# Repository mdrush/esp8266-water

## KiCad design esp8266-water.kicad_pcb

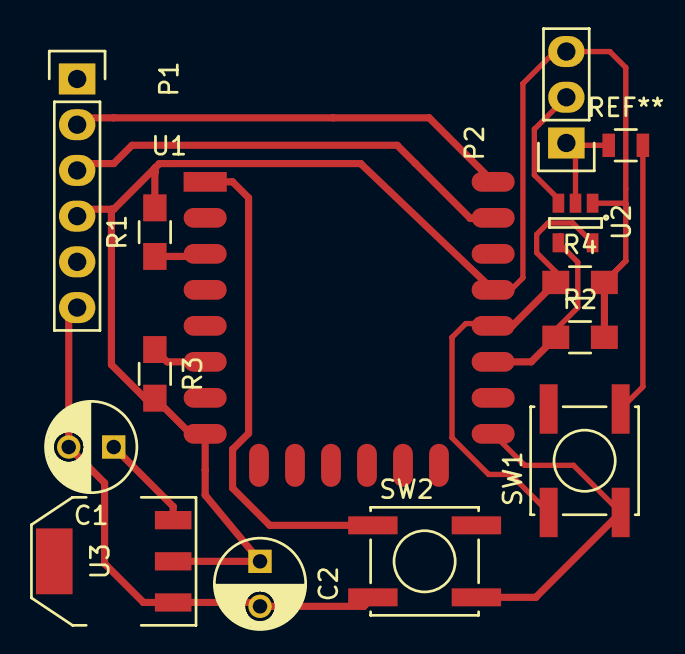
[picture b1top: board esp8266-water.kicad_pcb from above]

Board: 2 copper layers, 13 parts (0 on the bottom side), 10 nets.

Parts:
C1, C2: CP1; C_Radial_D5_L11_P2.5
P1: FTDI; Socket_Strip_Straight_1x06
P2: CONN_01X03; Socket_Strip_Straight_1x03
R1, R2, R3, R4: 10k; R_0805_HandSoldering
SW1, SW2: SW_PUSH; SW_SPST_EVPBF
U1: ESP-12E
U2: MCP3021A5T-E/OTCT-ND; SOT-23-5
U3: LD1117S33TR; SOT-223

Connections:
+3V3: C2.1, P1.4, P2.3, R1.2, R2.2, R3.2, R4.2, U1.8, U1.19, U2.1, U3.2
/GPIO0: R4.1, SW1.1, U1.18, U2.5
/GPIO2: R2.1, U1.17, U2.4
/RESET: R3.1, SW2.1, U1.1, U1.6
GND: C1.2, C2.2, P1.6, P2.1, SW1.2, SW2.2, U1.15, U2.2, U3.1
unnamed: C1.1, U3.3
unnamed: P1.2, U1.22
unnamed: P1.3, U1.21
unnamed: P2.2, U2.3
unnamed: R1.1, U1.3

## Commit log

2016-02-08 Adding initial layout
2016-02-12 added test code
